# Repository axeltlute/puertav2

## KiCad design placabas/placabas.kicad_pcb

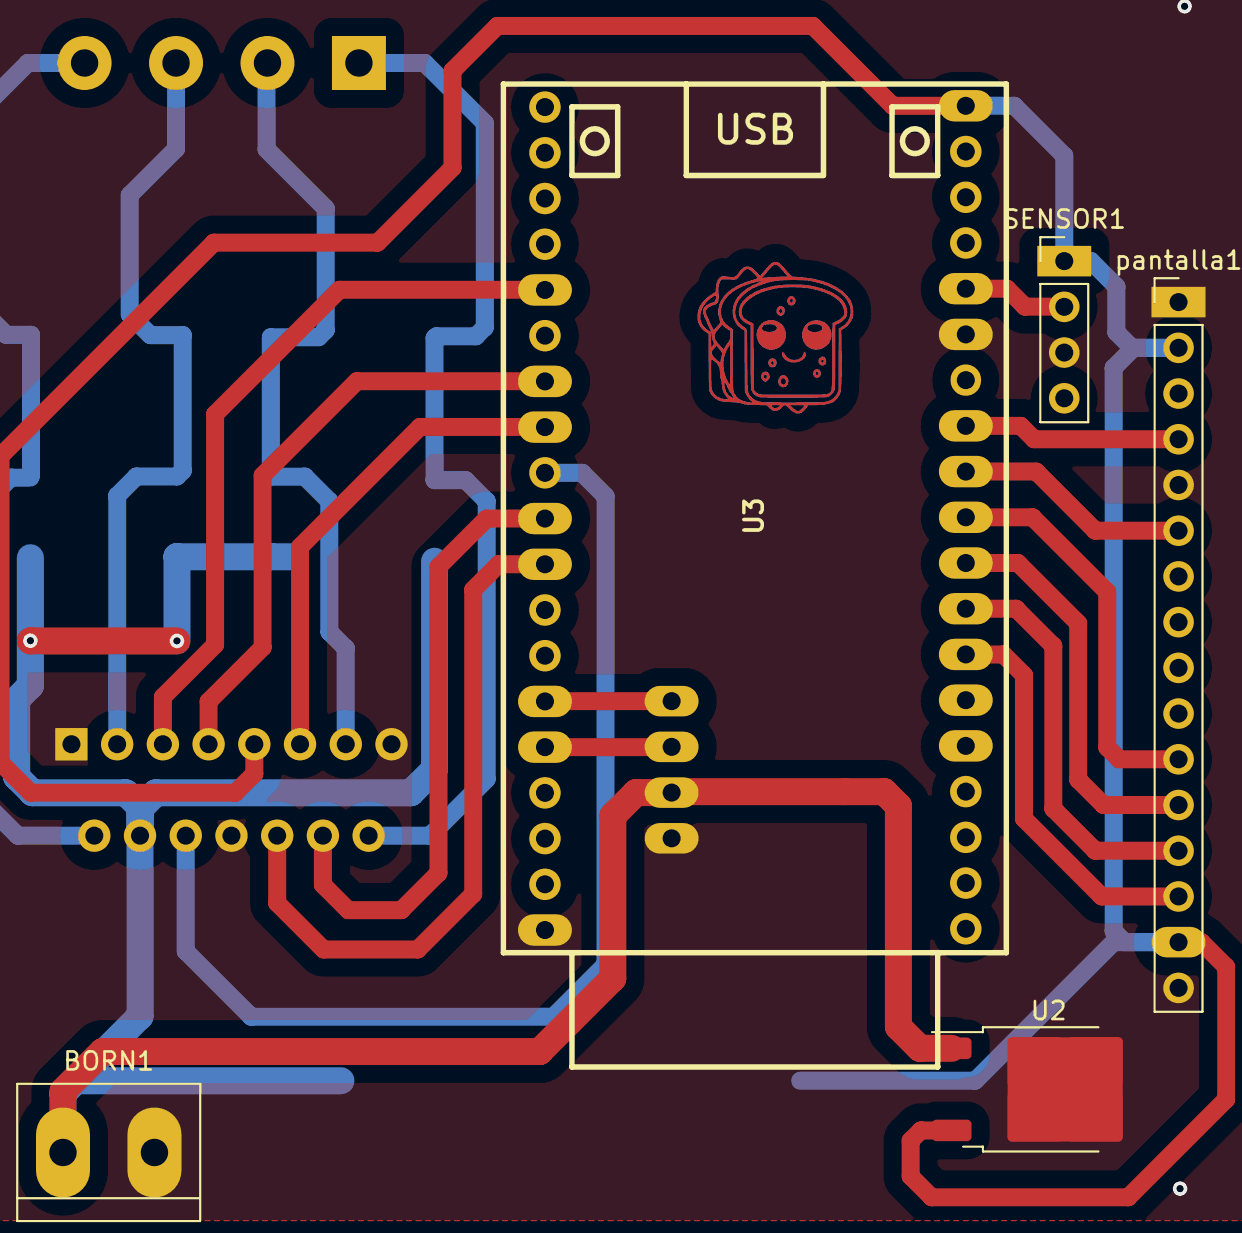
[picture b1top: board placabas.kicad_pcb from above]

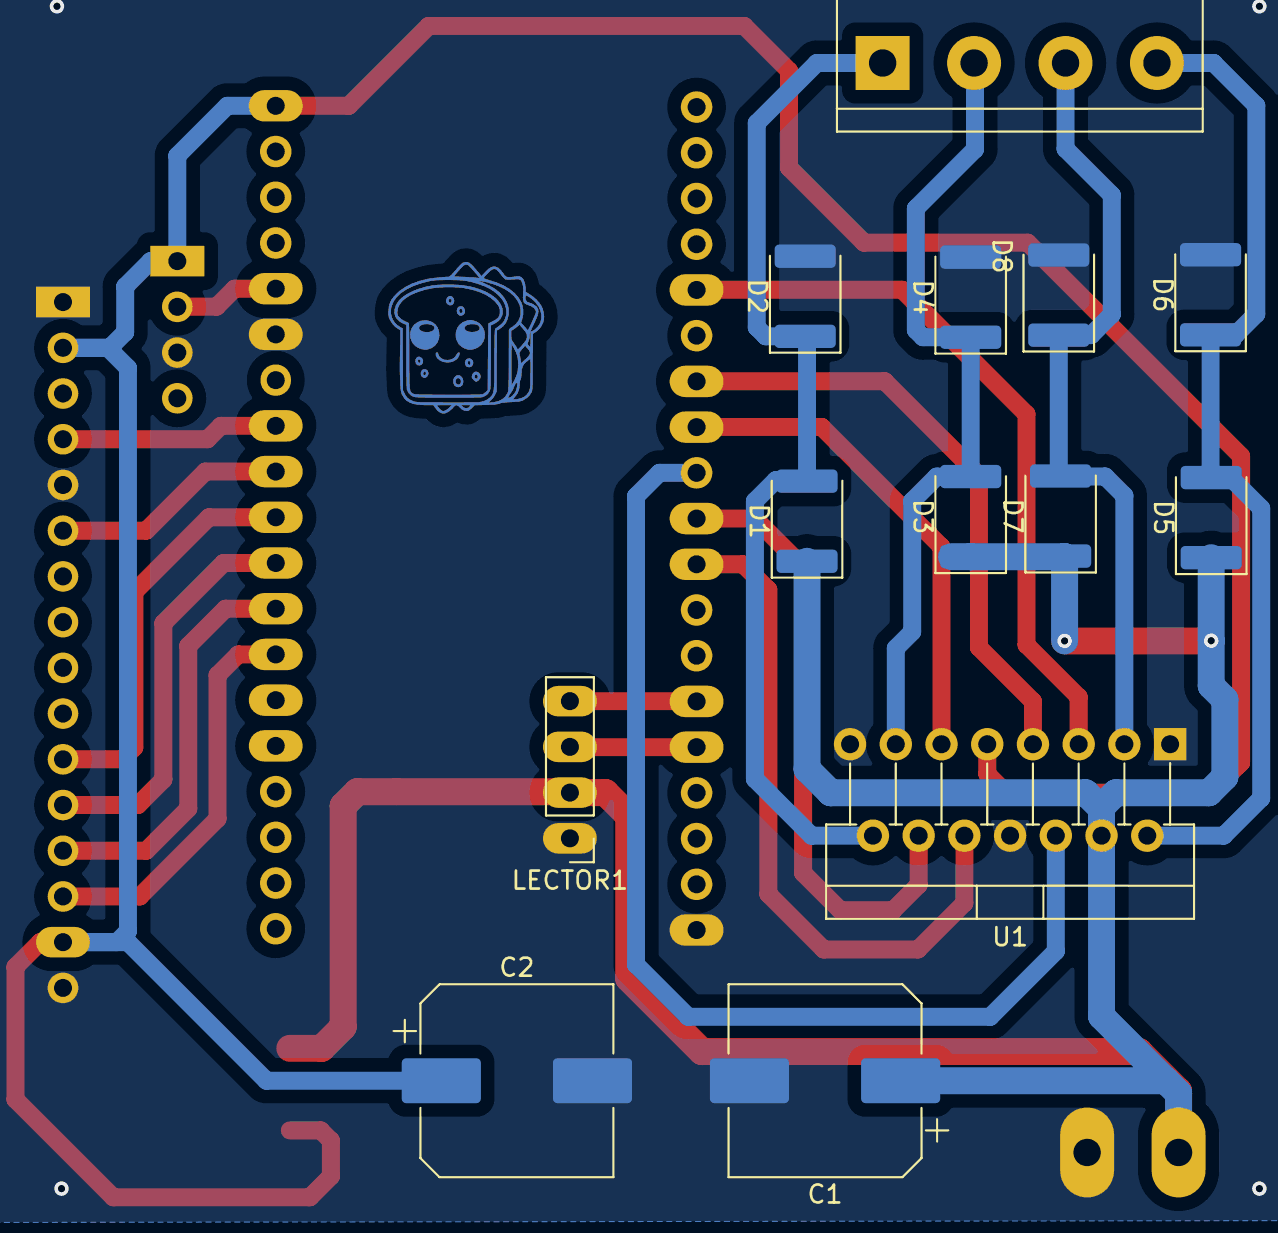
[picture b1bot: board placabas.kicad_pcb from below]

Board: 2 copper layers, 18 parts (13 on the bottom side), 22 nets.

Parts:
BORN1: TerminalBlock_bornier-2_P5.08mm
C1, C2: C; CP_Elec_10x12.5
D1, D2, D3, D4, D5, D6, D7, D8: 1N4001; D_1812_4532Metric_Pad1.30x3.40mm_HandSolder
LECTOR1: PinHeader_1x04_P2.54mm_Vertical
SENSOR1: PinHeader_1x04_P2.54mm_Vertical
U1: L298HN; TO-220-15_P2.54x2.54mm_StaggerOdd_Lead4.58mm_Vertical
U2: KA78M05_TO252; TO-252-2
U3: ESP32_DEVKITC
borneMM1: TerminalBlock_bornier-4_P5.08mm
pantalla1: PinHeader_1x16_P2.54mm_Vertical

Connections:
+5V: C2.1, SENSOR1.1, U1.9 (Vss), U2.3 (VO), U3.19 (5V), pantalla1.2, pantalla1.15
/D4: U3.10 (IO26), pantalla1.11
/D5: U3.9 (IO25), pantalla1.12
/D6: U3.8 (IO33), pantalla1.13
/D7: U3.7 (IO32), pantalla1.14
/E: U3.11 (IO27), pantalla1.6
/ENA: U1.6 (EnA), U3.28 (IO17)
/ENB: U1.11 (EnB), U3.27 (IO16)
/MA_1: U1.5 (IN1), U3.24 (IO02)
/MA_2: U1.7 (IN2), U3.26 (IO4)
/MB_1: U1.10 (IN3), U3.30 (IO18)
/MB_2: U1.12 (IN4), U3.29 (IO5)
/OUT_1: D5.2 (A), D6.1 (K), U1.2 (OUT1), borneMM1.4
/OUT_2: D7.2 (A), D8.1 (K), U1.3 (OUT2), borneMM1.3
/OUT_3: D3.2 (A), D4.1 (K), U1.13 (OUT3), borneMM1.2
/OUT_4: D1.2 (A), D2.1 (K), U1.14 (OUT4), borneMM1.1
/RS: U3.12 (IO14), pantalla1.4
/SCLL: LECTOR1.4, U3.33 (IO21)
/SDAL: LECTOR1.3, U3.34 (RXD0)
/TRIG: SENSOR1.2, U3.15 (IO13)
GND: BORN1.2, C1.2, C2.2, D2.2 (A), D4.2 (A), D6.2 (A), D8.2 (A), LECTOR1.1, SENSOR1.3, U1.1 (SENSE_A), U1.8 (GND), U1.15 (SENSE_B), U2.2 (GND), U3.14 (GND), U3.38 (GND), pantalla1.1, pantalla1.5, pantalla1.16
VCC: BORN1.1, C1.1, D1.1 (K), D3.1 (K), D5.1 (K), D7.1 (K), LECTOR1.2, U1.4 (Vs), U2.1 (VI)

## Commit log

2023-10-03 puertav2
